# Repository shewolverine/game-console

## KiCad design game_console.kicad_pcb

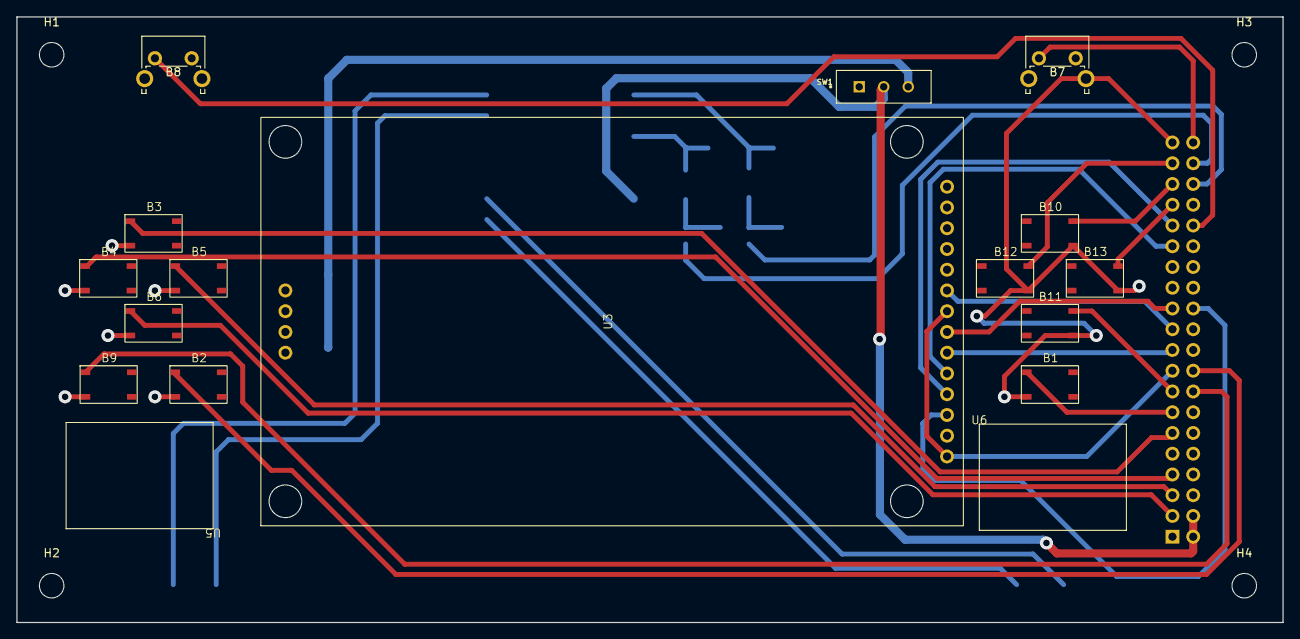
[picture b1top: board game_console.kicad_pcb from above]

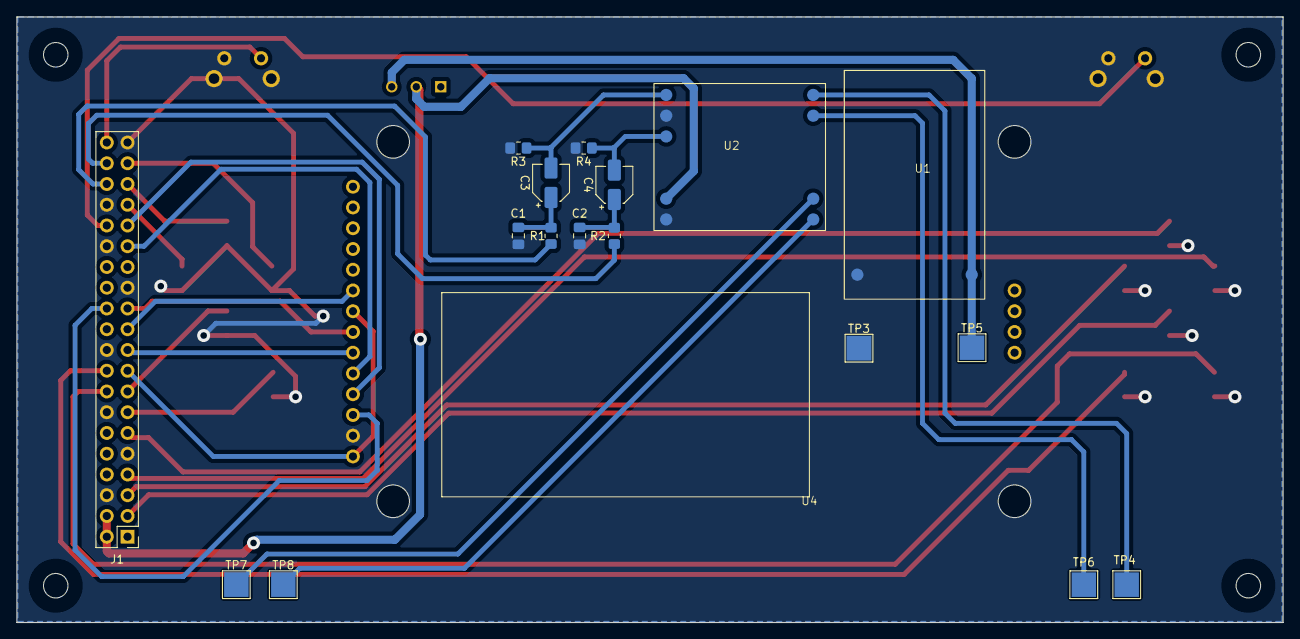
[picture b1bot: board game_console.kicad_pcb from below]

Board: 2 copper layers, 155.0 x 74.1 mm, 39 parts (18 on the bottom side), 33 nets.

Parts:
B1, B2, B3, B4, B5, B6, B9, B10, B11, B12, B13: 45x45x55
B7, B8: SW_Tactile_SPST_Angled_PTS645Vx58-2LFS
C1, C2: C; C_0805_2012Metric_Pad1.18x1.45mm_HandSolder
C3, C4: C; CP_Elec_4x5.4
H1, H2, H3, H4: MountingHole; MountingHole_3mm
J1: Conn_02x20_Row_Letter_First; PinSocket_2x20_P2.54mm_Vertical
R1, R2, R3, R4: R; R_0805_2012Metric_Pad1.20x1.40mm_HandSolder
SW1: SW_SPDT; SW_MINI-SPDT-SW
TP3, TP4, TP5, TP6, TP7, TP8: TestPoint; TestPoint_Pad_3.0x3.0mm
U1: tp4056
U2: pam8403
U3: ili9341
U4: pil
U5, U6: hoparlor

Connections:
+3.3V: J1.17, U3.7 (A(3.2V)), U3.14 (VCC)
+5V: J1.2, J1.4, SW1.2 (B), U2.8 (5V)
+BATT: SW1.3 (C), TP5.1, U1.3 (out+)
/A0: J1.29, U3.10 (A0)
/CLK: J1.23, U3.8 (SCL)
/CS: J1.24, U3.12 (CS)
/L: C3.2, R3.1, U2.5 (L)
/MISO: J1.21, U3.6 (MISO)
/MOSI: J1.19, U3.9 (MOSI)
/PWM0: J1.36, R1.1
/PWM1: J1.38, R2.1
/R: C4.2, R4.1, U2.7 (R)
/RST: J1.31, U3.11 (RST)
/audioL+: TP6.1, U2.2 (outL+)
/audioL-: TP4.1, U2.1 (outL-)
/audioR+: TP7.1, U2.3 (outR+)
/audioR-: TP8.1, U2.4 (outR-)
/bt_L_1: B3.1, J1.11
/bt_L_2: B4.1, J1.7
/bt_L_3: B5.1, J1.5
/bt_L_4: B6.1, J1.3
/bt_R_1: B10.3, J1.35
/bt_R_2: B12.3, J1.37
/bt_R_3: B11.3, J1.15
/bt_R_4: B13.3, J1.33
/bt_select: B2.1, J1.18
/bt_start: B1.1, J1.13
/r_a_L: B8.1, J1.32
/r_a_R: B7.1, J1.40
/r_a_Z: B9.1, J1.16
GND: B1.2, B2.2, B3.2, B4.2, B5.2, B6.2, B7.2, B7.3, B7.4, B8.2, B8.3, B8.4, B9.2, B10.4, B11.4, B12.4, B13.4, C1.2, C2.2, J1.6, J1.9, J1.14, J1.20, J1.25, J1.30, J1.34, J1.39, R3.2, R4.2, TP3.1, U1.6 (out-), U2.6 (GND), U2.9 (GND), U3.13 (GND)
unnamed: C1.1, C3.1, R1.2
unnamed: C2.1, C4.1, R2.2
